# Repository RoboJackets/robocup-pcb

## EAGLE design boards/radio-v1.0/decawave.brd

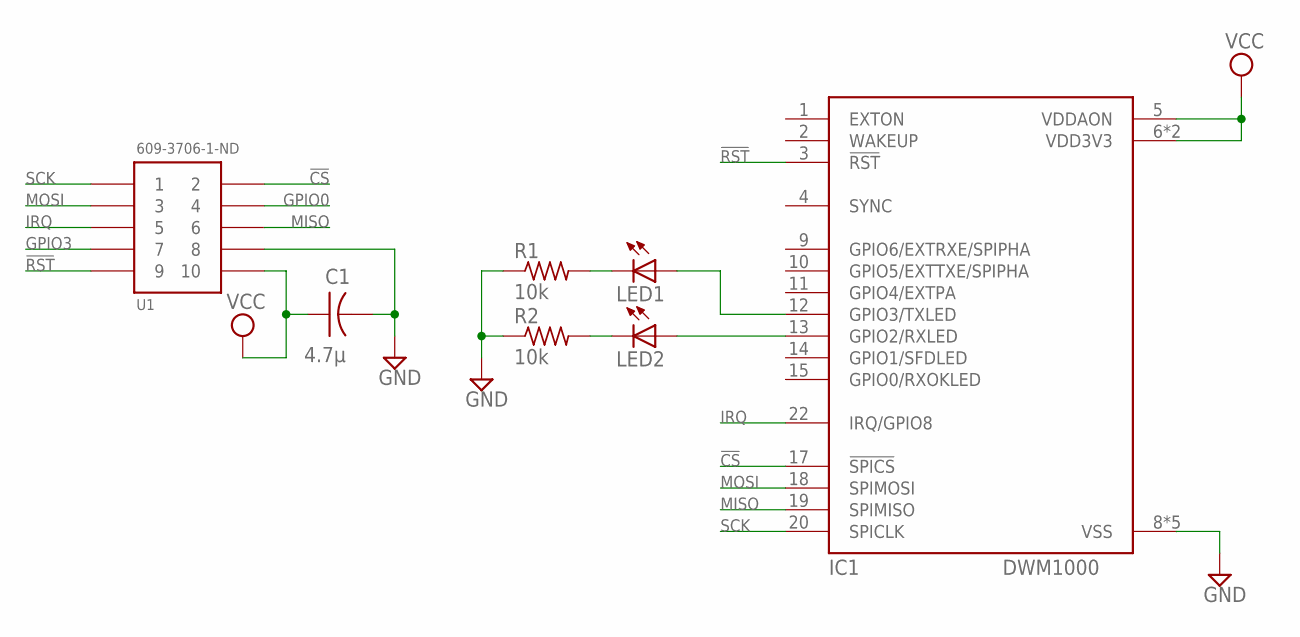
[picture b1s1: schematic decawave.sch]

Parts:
C1: 4.7µ; C0603
IC1: DWM1000
LED1, LED2: LEDCHIP-LED0805; CHIP-LED0805
R1, R2: 10k; R0603
U1: 609-3706-1-ND; 5X2_FEMALE

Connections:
!CS: IC1.17 (!SPICS), U1.2
!RST: IC1.3 (!RST), U1.9
GND: C1.2, IC1.8 (VSS), IC1.16 (VSS), IC1.21 (VSS), IC1.23 (VSS), IC1.24 (VSS), R1.1, R2.1, U1.8
GPIO0: U1.4
GPIO3: U1.7
IRQ: IC1.22 (IRQ/GPIO8), U1.5
MISO: IC1.19 (SPIMISO), U1.6
MOSI: IC1.18 (SPIMOSI), U1.3
unnamed: IC1.12 (GPIO3/TXLED), LED1.A
unnamed: IC1.13 (GPIO2/RXLED), LED2.A
unnamed: LED1.C, R1.2
unnamed: LED2.C, R2.2
SCK: IC1.20 (SPICLK), U1.1
VCC: C1.1, IC1.5 (VDDAON), IC1.6 (VDD3V3), IC1.7 (VDD3V3), U1.10

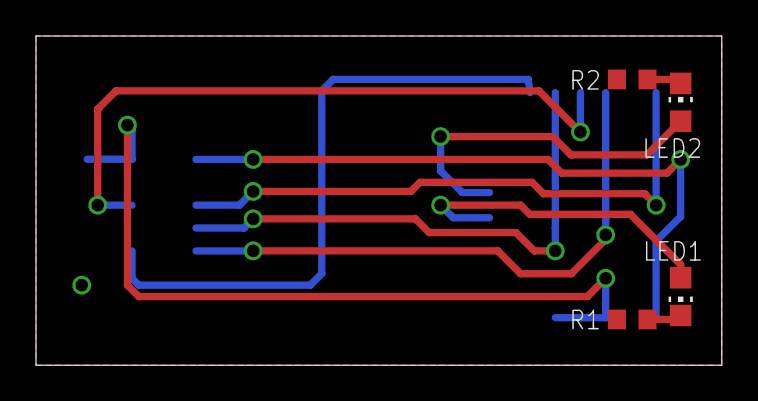
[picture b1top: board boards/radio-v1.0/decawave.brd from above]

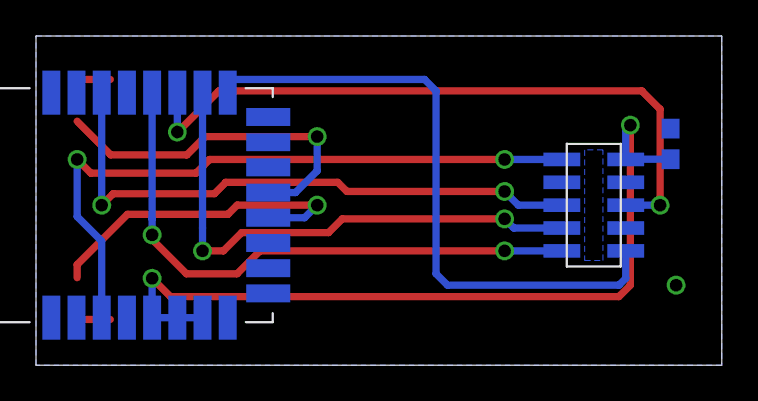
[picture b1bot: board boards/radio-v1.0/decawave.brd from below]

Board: 2 copper layers, 38.1 x 18.3 mm, 7 parts (3 on the bottom side), 12 nets.

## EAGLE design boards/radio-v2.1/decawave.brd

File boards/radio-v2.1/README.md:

# Radio Board

Board containing radio circuitry to communicate between robot(s) and base station

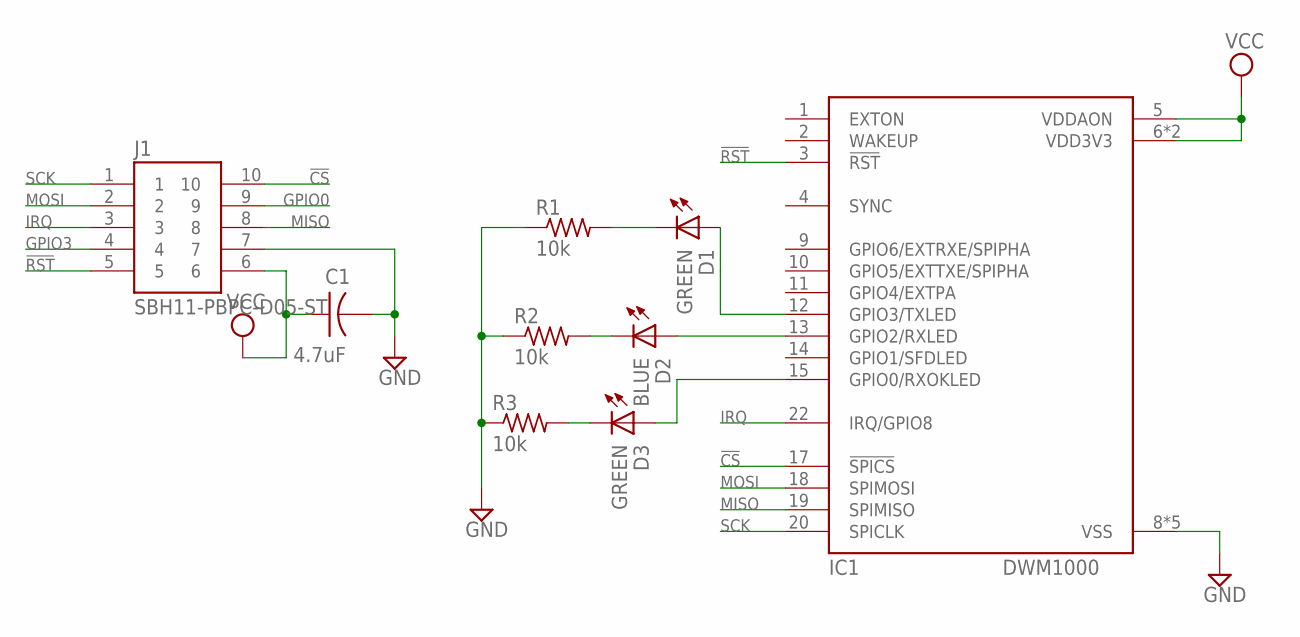
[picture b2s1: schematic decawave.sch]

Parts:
C1: 4.7uF; C0603
D1, D3: GREEN; CHIP-LED0603
D2: BLUE; CHIP-LED0603
IC1: DWM1000
J1: SBH11-PBPC-D05-ST; SFH11-*-D05-ST
R1, R2, R3: 10k; R0603

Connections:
!CS: IC1.17 (!SPICS), J1.10
!RST: IC1.3 (!RST), J1.5
GND: C1.2, IC1.8 (VSS), IC1.16 (VSS), IC1.21 (VSS), IC1.23 (VSS), IC1.24 (VSS), J1.7, R1.1, R2.1, R3.1
GPIO0: J1.9
GPIO3: J1.4
IRQ: IC1.22 (IRQ/GPIO8), J1.3
LED-RX: D2.A, IC1.13 (GPIO2/RXLED)
LED-RX-PRE: D2.C (K), R2.2
LED-RXOK: D3.A, IC1.15 (GPIO0/RXOKLED)
LED-RXOK-PRE: D3.C (K), R3.2
LED-TX: D1.A, IC1.12 (GPIO3/TXLED)
LED-TX-PRE: D1.C (K), R1.2
MISO: IC1.19 (SPIMISO), J1.8
MOSI: IC1.18 (SPIMOSI), J1.2
SCK: IC1.20 (SPICLK), J1.1
VCC: C1.1, IC1.5 (VDDAON), IC1.6 (VDD3V3), IC1.7 (VDD3V3), J1.6

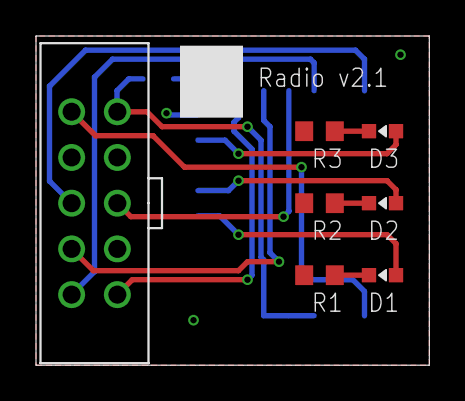
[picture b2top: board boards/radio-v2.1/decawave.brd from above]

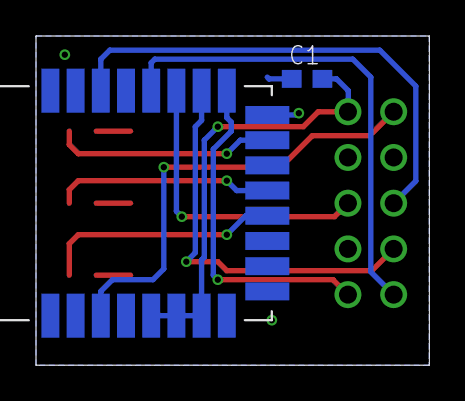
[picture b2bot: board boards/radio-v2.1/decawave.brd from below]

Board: 2 copper layers, 21.9 x 18.3 mm, 9 parts (2 on the bottom side), 14 nets.

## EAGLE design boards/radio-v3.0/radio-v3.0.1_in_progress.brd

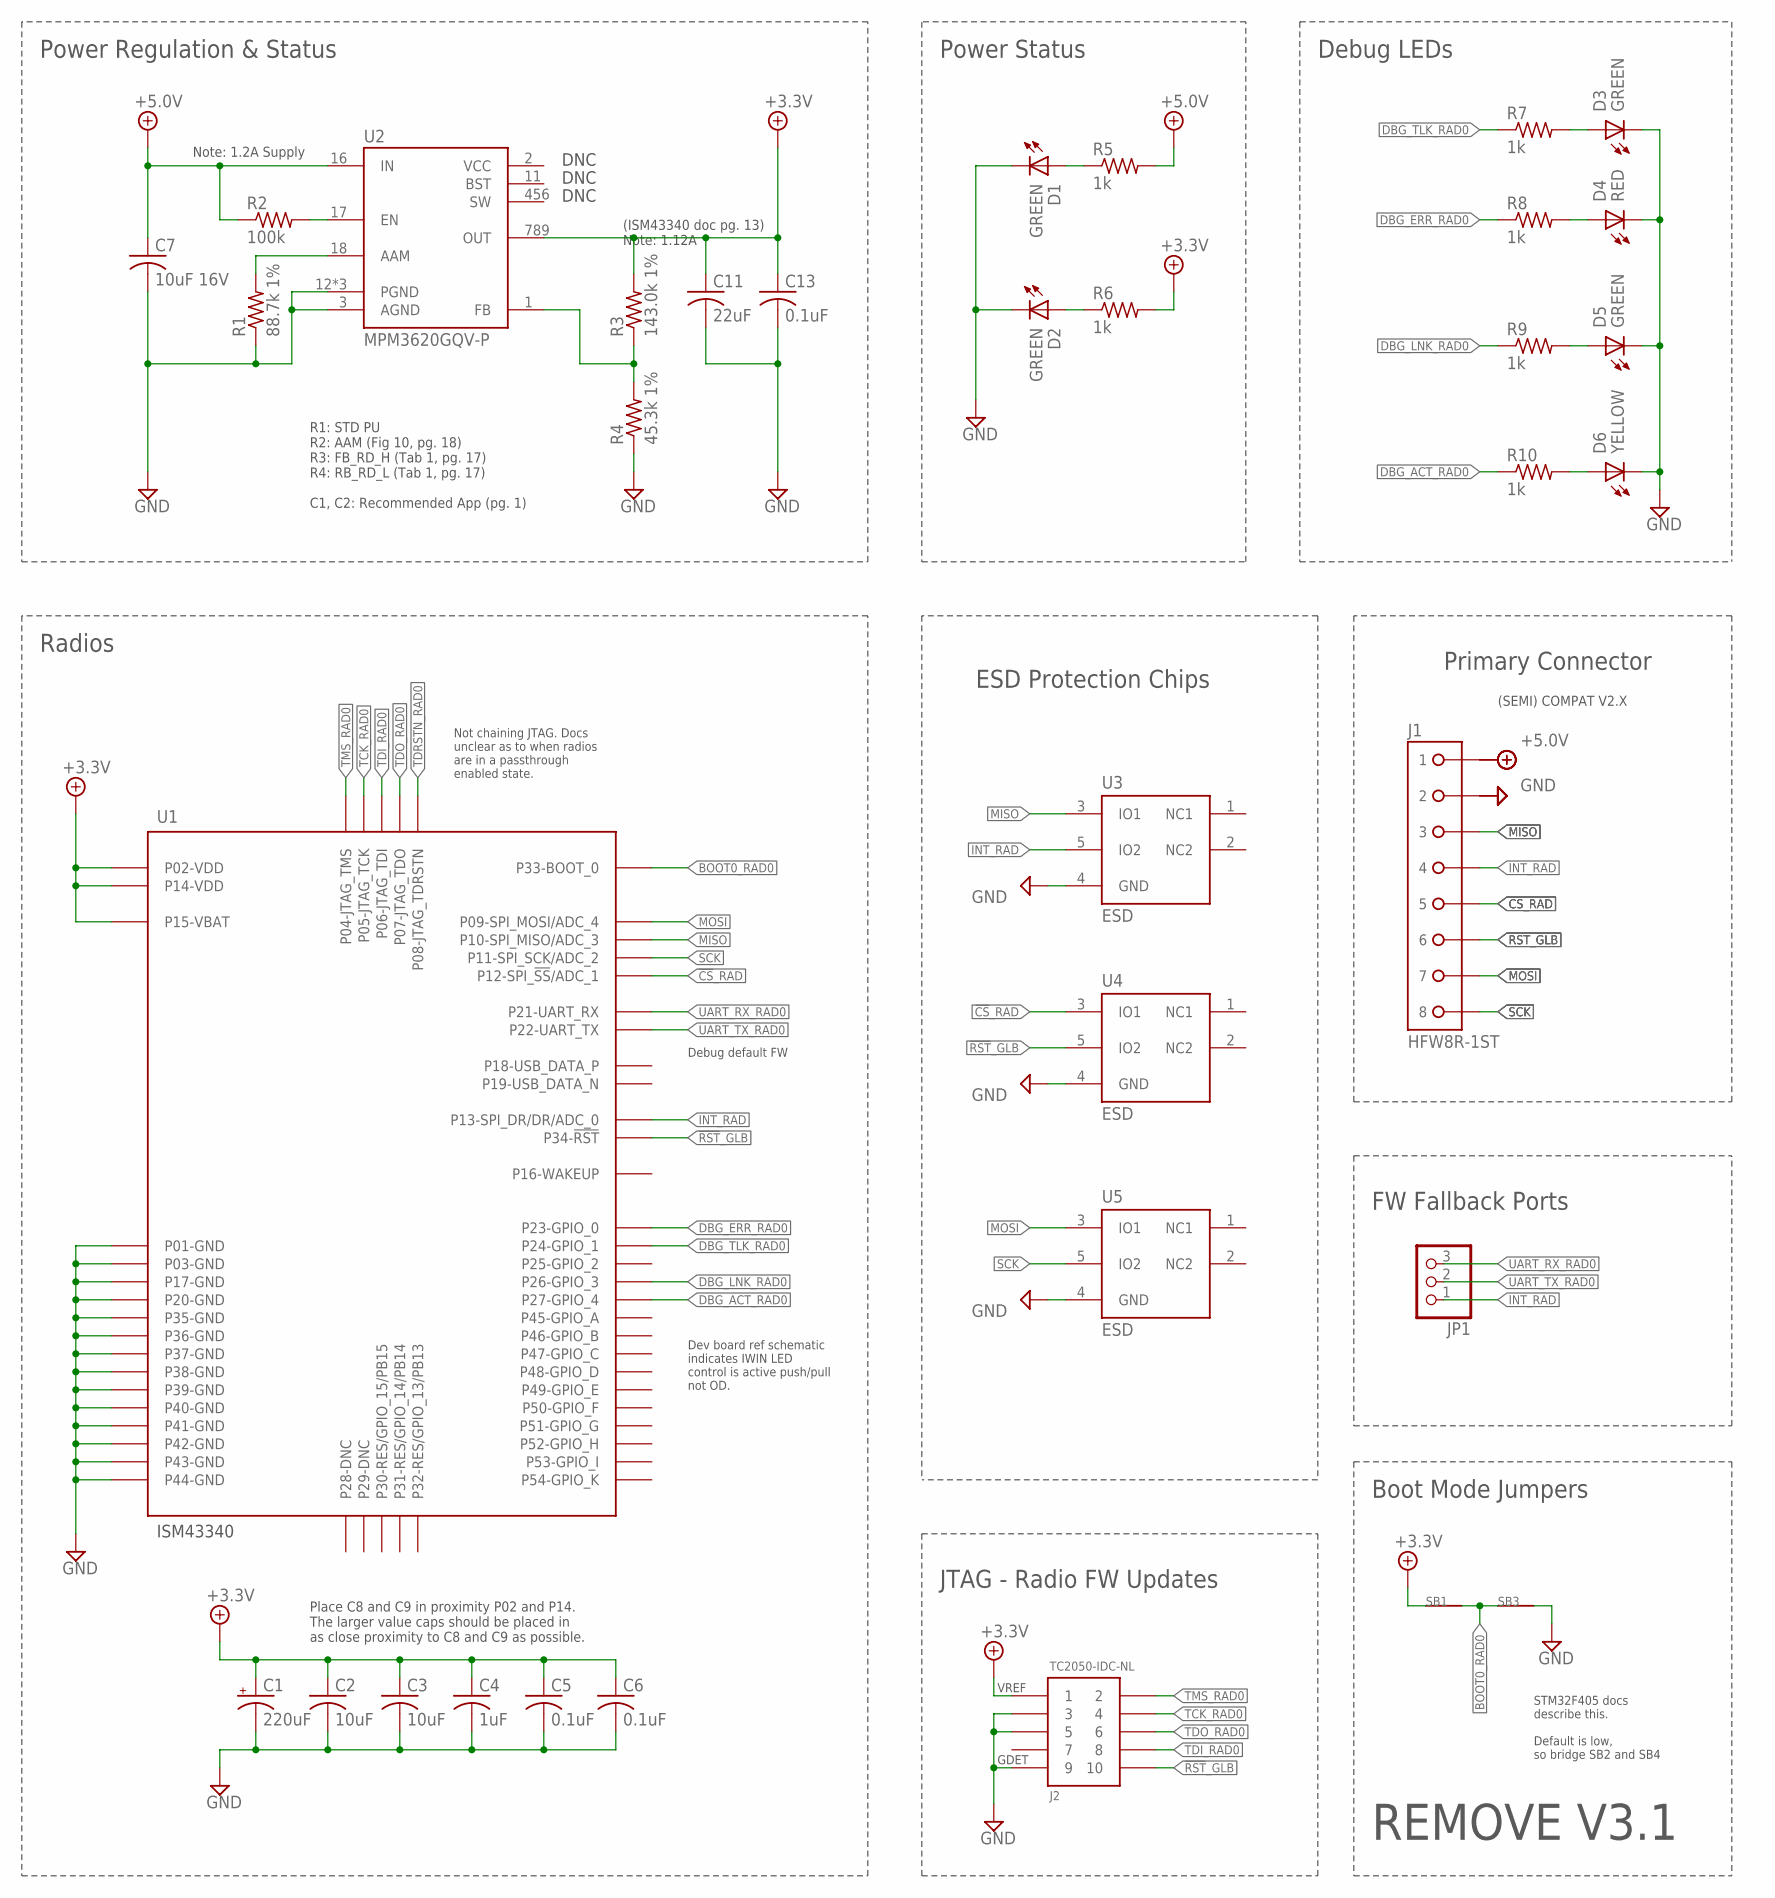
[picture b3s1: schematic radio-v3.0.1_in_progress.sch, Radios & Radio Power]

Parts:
C1: 220uF; ECA-0JM221-HGT_HORIZ
C2, C3: 10uF; C1210
C4: 1uF; C0603
C5, C6, C13: 0.1uF; C0603
C7: 10uF 16V; C1210
C11: 22uF; C1210
D1, D2, D3, D5: GREEN; CHIP-LED0603
D4: RED; CHIP-LED0603
D6: YELLOW; CHIP-LED0603
J1: HFW8R-1ST
J2: TC2050-IDC-NL
JP1: PINHD-1X3; 1X03
R1: 88.7k 1%; R0603
R2: 100k; R0603
R3: 143.0k 1%; R0603
R4: 45.3k 1%; R0603
R5, R6, R7, R8, R9, R10: 1k; R0603
SB1, SB3: SOLDERBRIDGESB0603; SB0603
U1: ISM43340
U2: MPM3620GQV-P
U3, U4, U5: ESD; SOT-553

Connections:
3V3_PWR_IND: D2.A, R6.1
5V_PWR_IND: D1.A, R5.1
!CS!_RAD: J1.5, U1.P$12 (P12-SPI_!SS!/ADC_1)
!RST!_GLB: J1.6, J2.P$10 (10), U1.P$34 (P34-!RST!)
+3.3V: C1.P$1 (+), C2.1, C3.1, C4.1, C5.1, C6.1, C11.1, C13.1, J2.P$1 (1), R3.2, R6.2, SB1.1, U1.P$2 (P02-VDD), U1.P$14 (P14-VDD), U1.P$15 (P15-VBAT), U2.789 (OUT)
+5.0V: C7.1, J1.1, R2.1, R5.2, U2.16 (IN)
AAM: R1.2, U2.18 (AAM)
BOOT0_RAD0: SB1.2, SB3.1, U1.P$33 (P33-BOOT_0)
DBG_ACT_RAD0: R10.1, U1.P$27 (P27-GPIO_4)
DBG_ERR_RAD0: R8.1, U1.P$23 (P23-GPIO_0)
DBG_LNK_RAD0: R9.1, U1.P$26 (P26-GPIO_3)
DBG_TLK_RAD0: R7.1, U1.P$24 (P24-GPIO_1)
EN: R2.2, U2.17 (EN)
FB: R3.1, R4.2, U2.1 (FB)
GND: C1.P$2 (-), C2.2, C3.2, C4.2, C5.2, C6.2, C7.2, C11.2, C13.2, D1.C (K), D2.C (K), D3.C (K), D4.C (K), D5.C (K), D6.C (K), J1.2, J2.P$3 (3), J2.P$5 (5), J2.P$9 (9), R1.1, R4.1, SB3.2, U1.P$1 (P01-GND), U1.P$3 (P03-GND), U1.P$17 (P17-GND), U1.P$20 (P20-GND), U1.P$35 (P35-GND), U1.P$36 (P36-GND), U1.P$37 (P37-GND), U1.P$38 (P38-GND), U1.P$39 (P39-GND), U1.P$40 (P40-GND), U1.P$41 (P41-GND), U1.P$42 (P42-GND), U1.P$43 (P43-GND), U1.P$44 (P44-GND), U2.3 (AGND), U2.12 (PGND), U2.13 (PGND), U2.14 (PGND), U3.4 (GND), U4.4 (GND), U5.4 (GND)
INT_RAD: J1.4, JP1.1, U1.P$13 (P13-SPI_DR/DR/ADC_0)
MISO: J1.3, U1.P$10 (P10-SPI_MISO/ADC_3)
MOSI: J1.7, U1.P$9 (P09-SPI_MOSI/ADC_4)
unnamed: D3.A, R7.2
unnamed: D4.A, R8.2
unnamed: D5.A, R9.2
unnamed: D6.A, R10.2
SCK: J1.8, U1.P$11 (P11-SPI_SCK/ADC_2)
TCK_RAD0: J2.P$4 (4), U1.P$5 (P05-JTAG_TCK)
TDI_RAD0: J2.P$8 (8), U1.P$6 (P06-JTAG_TDI)
TDO_RAD0: J2.P$6 (6), U1.P$7 (P07-JTAG_TDO)
TDRSTN_RAD0: U1.P$8 (P08-JTAG_TDRSTN)
TMS_RAD0: J2.P$2 (2), U1.P$4 (P04-JTAG_TMS)
UART_RX_RAD0: JP1.3, U1.P$21 (P21-UART_RX)
UART_TX_RAD0: JP1.2, U1.P$22 (P22-UART_TX)

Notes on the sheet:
DNC
Primary Connector
Power Regulation & Status
Power Status
Note: 1.2A Supply
(ISM43340 doc pg. 13) Note: 1.12A
R1: STD PU R2: AAM (Fig 10, pg. 18) R3: FB_RD_H (Tab 1, pg. 17) R4: RB_RD_L (Tab 1, pg. 17) C1, C2: Recommended App (pg. 1)
Radios
Place C8 and C9 in proximity P02 and P14. The larger value caps should be placed in as close proximity to C8 and C9 as possible.
Debug LEDs
VREF
GDET
JTAG - Radio FW Updates
Boot Mode Jumpers
FW Fallback Ports
Dev board ref schematic indicates IWIN LED control is active push/pull not OD.
Not chaining JTAG. Docs unclear as to when radios are in a passthrough enabled state.
Debug default FW
STM32F405 docs describe this. Default is low, so bridge SB2 and SB4
REMOVE V3.1
(SEMI) COMPAT V2.X
ESD Protection Chips

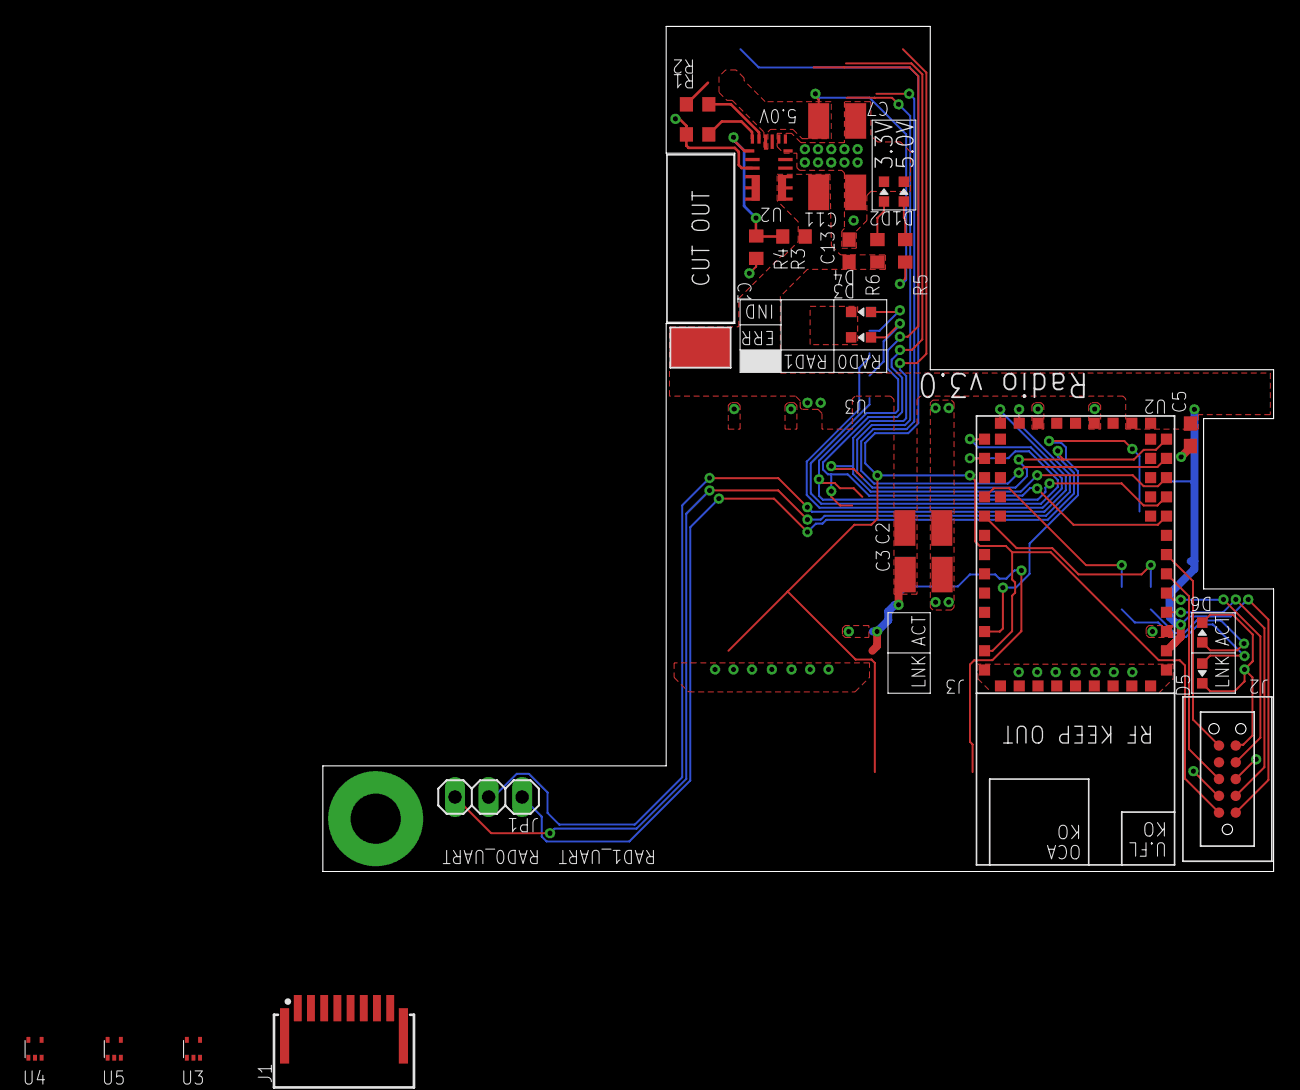
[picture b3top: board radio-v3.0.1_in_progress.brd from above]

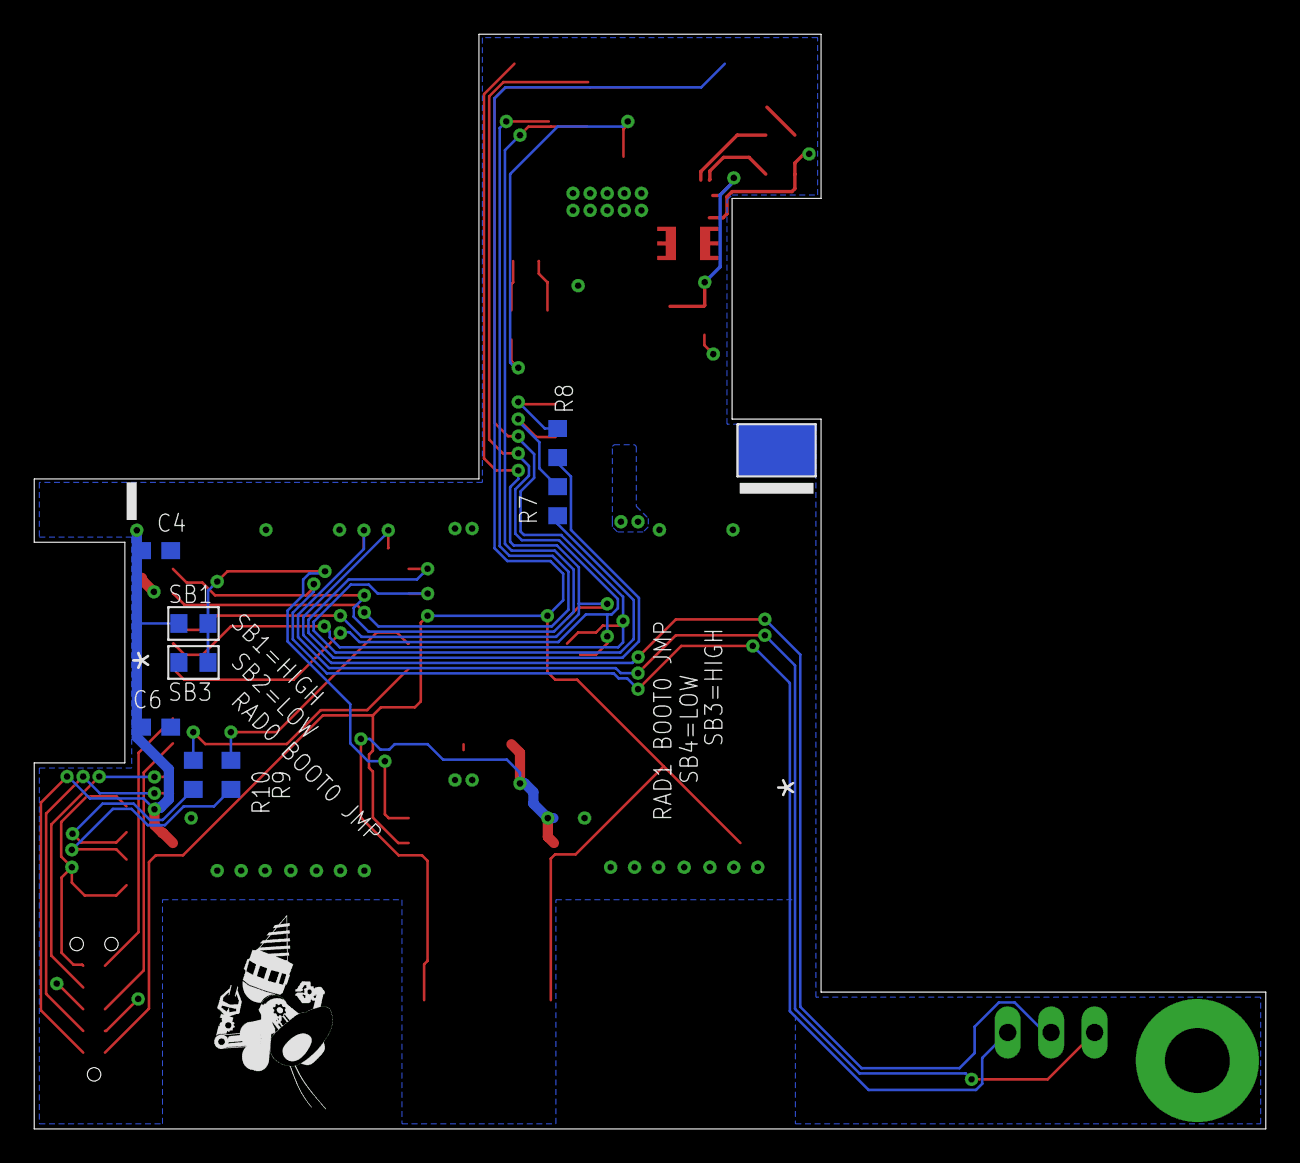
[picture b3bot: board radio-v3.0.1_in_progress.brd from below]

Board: 2 copper layers, 72.0 x 64.0 mm, 36 parts (9 on the bottom side), 29 nets.

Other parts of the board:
U$1: ROBOBUZZ_0.6X
